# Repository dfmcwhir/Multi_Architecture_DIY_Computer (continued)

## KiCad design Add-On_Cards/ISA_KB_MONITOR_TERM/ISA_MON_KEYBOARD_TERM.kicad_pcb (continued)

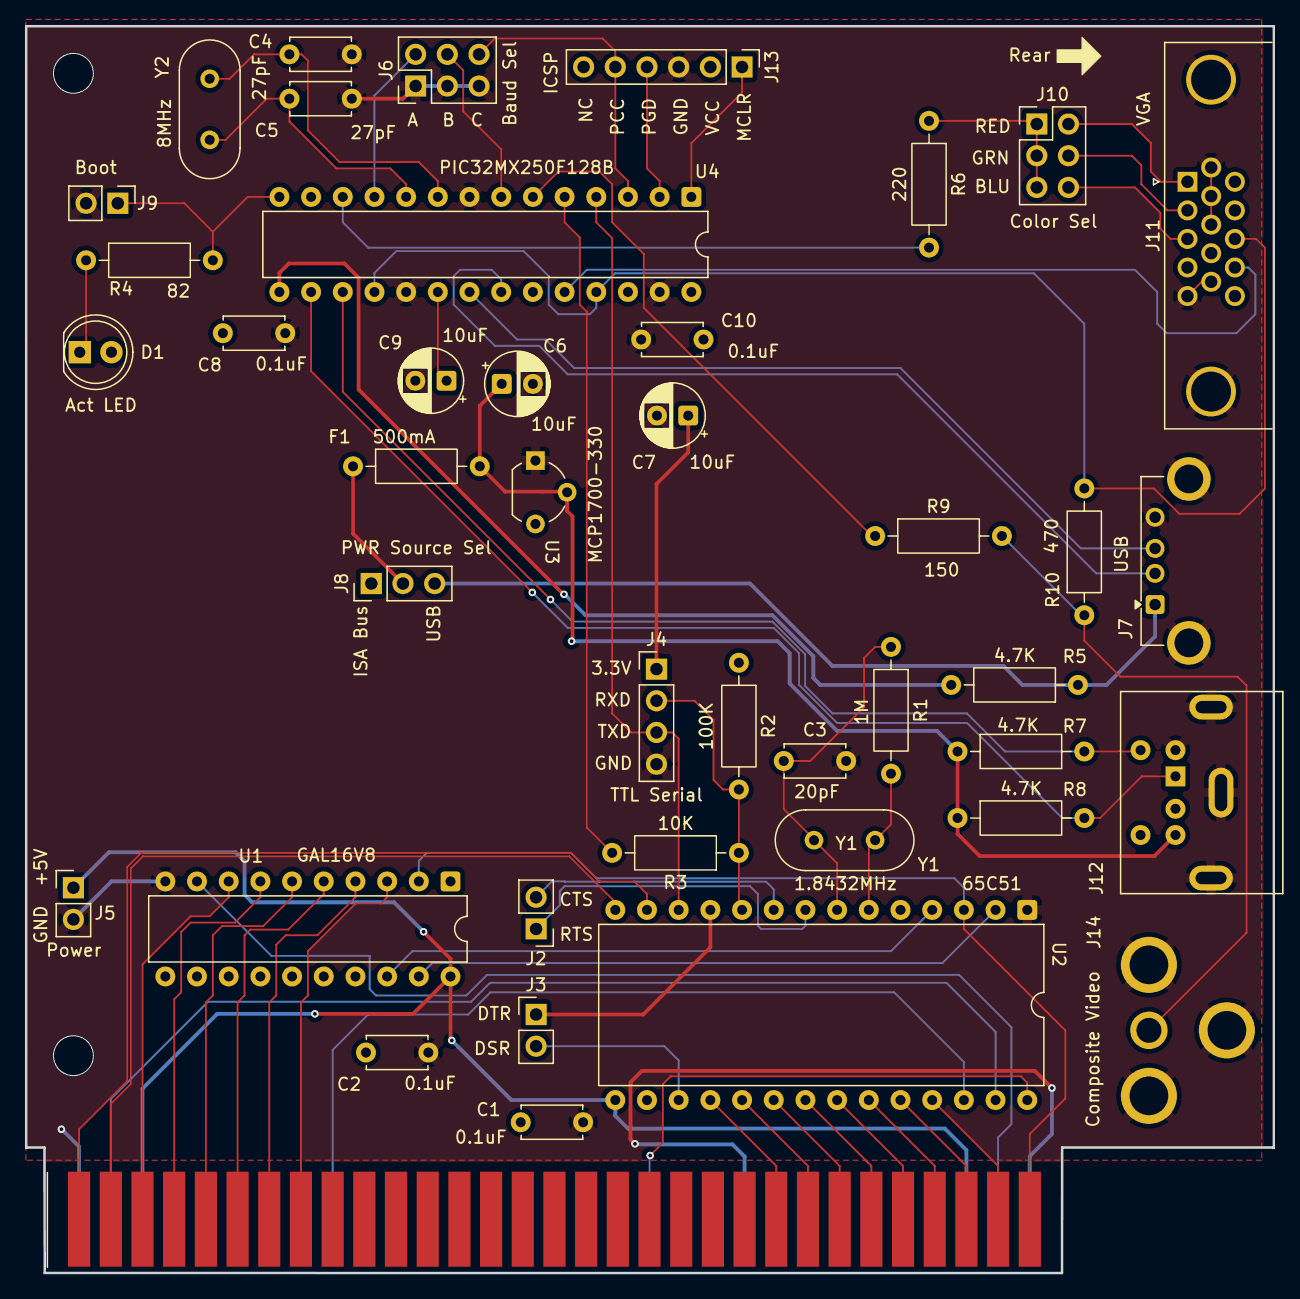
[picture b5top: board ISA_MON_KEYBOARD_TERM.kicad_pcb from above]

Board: 2 copper layers, 100.0 x 99.9 mm, 44 parts (0 on the bottom side), 62 nets.

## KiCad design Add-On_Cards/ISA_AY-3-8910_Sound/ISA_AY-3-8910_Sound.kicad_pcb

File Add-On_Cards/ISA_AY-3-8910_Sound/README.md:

<h2>AY-3-8910 sound card</h2>

<p>This a new card that That is in the process of being tested with the ISA_6502_CPU Rev2 card. For this version of the card the I/O ports A and B were broken out and can be used for general purpose IO. The SPO256 speech chip was added to this version of the board as well.</p>

<h2>Known Bugs</h2>
<p>
  <li>Rev0 of this card ran fine at 2MHz, but to make this card capable of running at higher clock speeds, the PLD introduces a /WAIT signal. For the 6502_CPU_Rev2 card that means the J1 Wait_Sel jumper should be on pins 2-3. However, on the 8085 and Z80 cards that won't work. The current 8085 CPU card doesn't have the /WAIT or /STRETCH signals implemented at all. For the Z80 card both the /WAIT and /STRETCH signals stop the CLK, so the fix is to cut the trace to pin1 of the PLD and attach pin1 of the PLD to the TC (2XOSC) pin on the bus. That modification should also still work when using the 6502_CPU_Rev2 but with JP1 Wait_Sel set to pin 1-2. To make it work with the current 8085 card, it probably requires keeping the CPU speed <3MHz and updating the PLD to not use the /WAIT logic. My current 8085 card uses a 4.9152MHz crystal so the clock is ~2.45MHz, but I haven't tested it with the sound card yet. </li>
<li>Combining the AY3 and SPO256 into a single channel of audio using the mono/stereo jumper doesn't seem to work (I didn't really think it would)</li></p>

<h2>Resources</h2>
<table><thead><tr><th>Address</th><th>Function</th></tr></thead>
<tr><td>7F22</td><td>AY3 Command Register</td></tr>
<tr><td>7F23</td><td>AY3 Data Register</td></tr>
<tr><td>7F26</td><td>SPO256 command/status register</td></tr>
</table>

<p>The SPO256 can use IRQ7 but installing a jumper, but it isn't clear if that will be necessary or desirable.</p>

<h2>Testing Status:</h2>
<li>Basic operation has been tested with the ISA_6502_CPU Rev2 card</li>
<li>AY-3-8910 Port A and B IO hasn't been tested</li>
<li>Amplified output hasn't been tested yet, only the line out</li>
<li>SPO256 speech is pretty quite through the line out, not sure if that is to be expected or if it can be fixed</li>

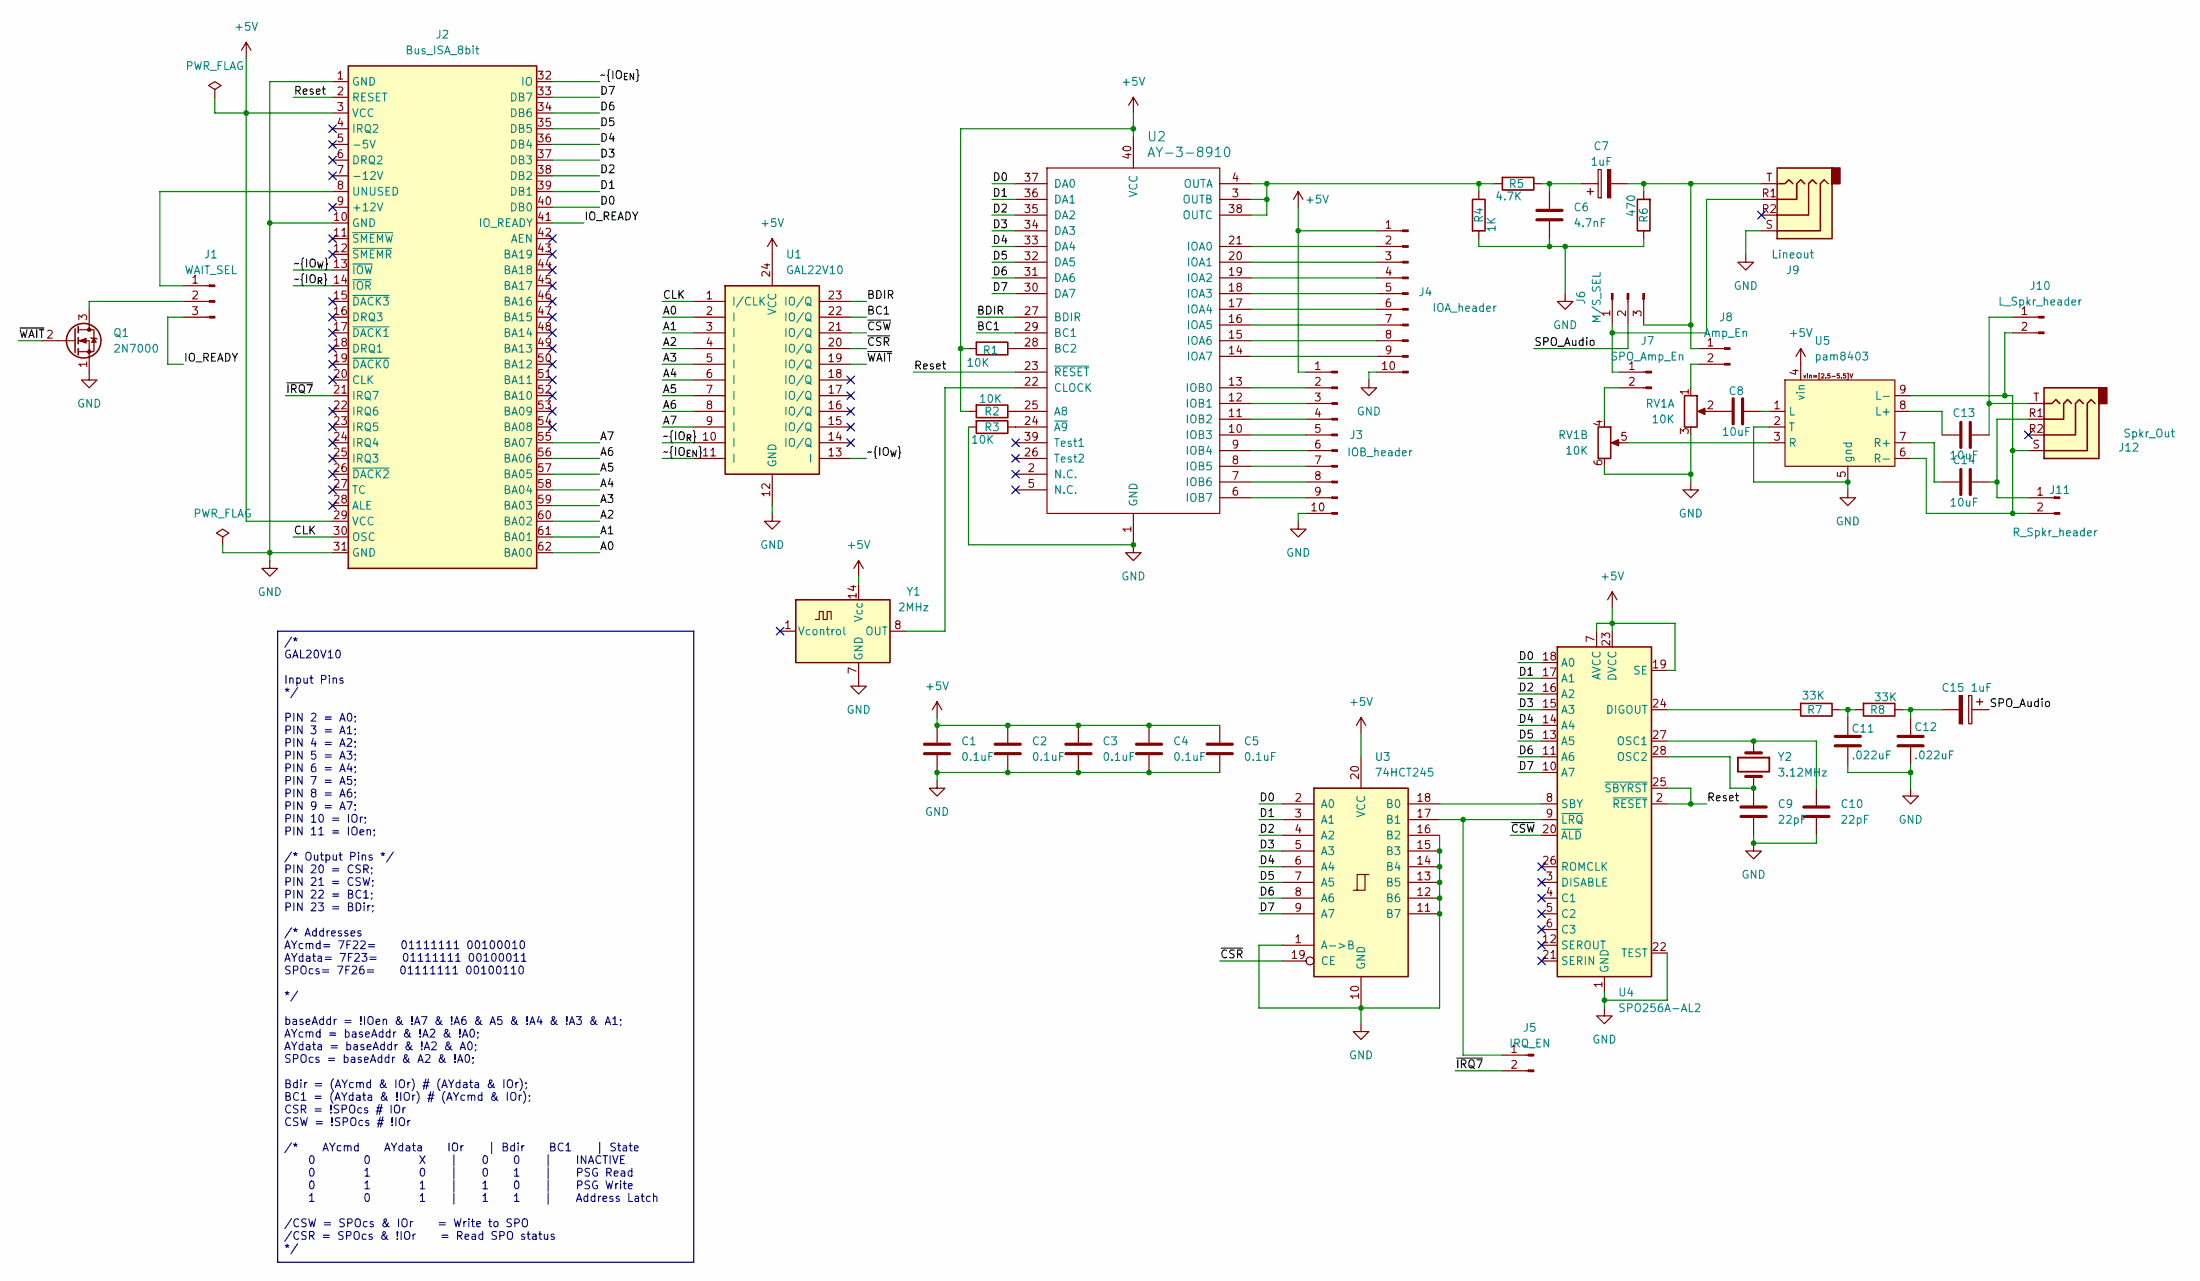
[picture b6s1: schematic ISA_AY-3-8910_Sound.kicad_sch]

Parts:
C1, C2, C3, C4, C5: 0.1uF; C_Disc_D4.7mm_W2.5mm_P5.00mm
C6: 4.7nF; C_Disc_D4.7mm_W2.5mm_P5.00mm
C7, C15: 1uF; CP_Radial_D6.3mm_P2.50mm
C8, C13, C14: 10uF; C_Disc_D4.7mm_W2.5mm_P5.00mm
C9, C10: 22pF; C_Disc_D4.7mm_W2.5mm_P5.00mm
C11, C12: .022uF; C_Disc_D4.7mm_W2.5mm_P5.00mm
J1: WAIT_SEL; PinHeader_1x03_P2.54mm_Vertical
J2: Bus_ISA_8bit; BUS_8-bit_ISA_CARD
J3: IOB_header; PinHeader_1x10_P2.54mm_Vertical
J4: IOA_header; PinHeader_1x10_P2.54mm_Vertical
J5: IRQ_EN; PinHeader_1x02_P2.54mm_Vertical
J6: M/S_SEL; PinHeader_1x03_P2.54mm_Vertical
J7: SPO_Amp_En; PinHeader_1x02_P2.54mm_Vertical
J8: Amp_En; PinHeader_1x02_P2.54mm_Vertical
J9: Lineout; Jack_3.5mm_PJ320E_Horizontal
J10: L_Spkr_header; PinHeader_1x02_P2.54mm_Vertical
J11: Spkr_Out; Jack_3.5mm_PJ320E_Horizontal
J12: R_Spkr_header; PinHeader_1x02_P2.54mm_Vertical
Q1: 2N7000; TO-92_Inline_Wide
R1, R2, R3: 10K; R_Axial_DIN0207_L6.3mm_D2.5mm_P10.16mm_Horizontal
R4: 1K; R_Axial_DIN0207_L6.3mm_D2.5mm_P10.16mm_Horizontal
R5: 4.7K; R_Axial_DIN0207_L6.3mm_D2.5mm_P10.16mm_Horizontal
R6: 470; R_Axial_DIN0207_L6.3mm_D2.5mm_P10.16mm_Horizontal
R7, R8: 33K; R_Axial_DIN0207_L6.3mm_D2.5mm_P10.16mm_Horizontal
RV1: 10K; Potentiometer_Alps_RK097_Dual_Horizontal
U1: GAL22V10; DIP-24_W7.62mm
U2: AY-3-8910; DIP-40_W15.24mm
U3: 74HCT245; DIP-20_W7.62mm
U4: SPO256A-AL2; DIP-28_W15.24mm
U5: pam8403
Y1: 2MHz; Oscillator_DIP-14
Y2: 3.12MHz; Crystal_HC18-U_Vertical

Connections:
+5V: C1.1, C2.1, C3.1, C4.1, C5.1, J2.3 (VCC), J2.29 (VCC), J3.1, J4.1, R1.2, R2.2, U1.24 (VCC), U2.40 (VCC), U3.20 (VCC), U4.7 (AVCC), U4.19 (SE), U4.23 (DVCC), U5.4 (vin), Y1.14 (Vcc)
/A0: J2.62 (BA00), U1.2 (I)
/A1: J2.61 (BA01), U1.3 (I)
/A2: J2.60 (BA02), U1.4 (I)
/A3: J2.59 (BA03), U1.5 (I)
/A4: J2.58 (BA04), U1.6 (I)
/A5: J2.57 (BA05), U1.7 (I)
/A6: J2.56 (BA06), U1.8 (I)
/A7: J2.55 (BA07), U1.9 (I)
/BC1: U1.22 (IO/Q), U2.29 (BC1)
/BDIR: U1.23 (IO/Q), U2.27 (BDIR)
/CLK: J2.30 (OSC), U1.1 (I/CLK)
/D0: J2.40 (DB0), U2.37 (DA0), U3.2 (A0), U4.18 (A0)
/D1: J2.39 (DB1), U2.36 (DA1), U3.3 (A1), U4.17 (A1)
/D2: J2.38 (DB2), U2.35 (DA2), U3.4 (A2), U4.16 (A2)
/D3: J2.37 (DB3), U2.34 (DA3), U3.5 (A3), U4.15 (A3)
/D4: J2.36 (DB4), U2.33 (DA4), U3.6 (A4), U4.14 (A4)
/D5: J2.35 (DB5), U2.32 (DA5), U3.7 (A5), U4.13 (A5)
/D6: J2.34 (DB6), U2.31 (DA6), U3.8 (A6), U4.11 (A6)
/D7: J2.33 (DB7), U2.30 (DA7), U3.9 (A7), U4.10 (A7)
/IO_READY: J1.3, J2.41 (IO_READY)
/Reset: J2.2 (RESET), U2.23 (~RESET), U4.2 (~RESET), U4.25 (~SBYRST)
/SPO_Audio: C15.1, J6.2
/~CSR: U1.20 (IO/Q), U3.19 (CE)
/~CSW: U1.21 (IO/Q), U4.20 (~ALD)
/~IO_{EN}: J2.32 (IO), U1.11 (I)
/~IO_{R}: J2.14 (~IOR), U1.10 (I)
/~IO_{W}: J2.13 (~IOW), U1.13 (I)
/~IRQ7: J2.21 (IRQ7), J5.2
/~WAIT: Q1.2 (G), U1.19 (IO/Q)
GND: C1.2, C2.2, C3.2, C4.2, C5.2, C6.2, C9.2, C10.2, C11.2, C12.2, J2.1 (GND), J2.10 (GND), J2.31 (GND), J3.10, J4.10, J9.S, Q1.1 (S), R3.2, R4.2, R6.1, RV1.3, RV1.6, U1.12 (GND), U2.1 (GND), U3.1 (A->B), U3.10 (GND), U3.11 (B7), U3.12 (B6), U3.13 (B5), U3.14 (B4), U3.15 (B3), U3.16 (B2), U4.1 (GND), U4.22 (TEST), U5.2 (T), U5.5 (gnd), Y1.7 (GND)
unnamed: C6.1, C7.1, R5.1
unnamed: C8.2, RV1.2
unnamed: C11.1, R7.1, R8.2
unnamed: C12.1, C15.2, R8.1
unnamed: J1.1, J2.8 (UNUSED)
unnamed: J1.2, Q1.3 (D)
unnamed: J3.2, U2.13 (IOB0)
unnamed: J3.3, U2.12 (IOB1)
unnamed: J3.4, U2.11 (IOB2)
unnamed: J3.5, U2.10 (IOB3)
unnamed: J3.6, U2.9 (IOB4)
unnamed: J3.7, U2.8 (IOB5)
unnamed: J3.8, U2.7 (IOB6)
unnamed: J3.9, U2.6 (IOB7)
unnamed: J4.2, U2.21 (IOA0)
unnamed: J4.3, U2.20 (IOA1)
unnamed: J4.4, U2.19 (IOA2)
unnamed: J4.5, U2.18 (IOA3)
unnamed: J4.6, U2.17 (IOA4)
unnamed: J4.7, U2.16 (IOA5)
unnamed: J4.8, U2.15 (IOA6)
unnamed: J4.9, U2.14 (IOA7)
unnamed: J5.1, U3.17 (B1), U4.9 (~LRQ)
unnamed: J6.1, J7.1, J9.R1
unnamed: C7.2, J6.3, J8.1, J9.T, R6.2
unnamed: J7.2, RV1.4
unnamed: J8.2, RV1.1
unnamed: C13.1, J10.1, J11.T
unnamed: J10.2, J11.S, J12.2, U5.6 (R-), U5.9 (L-)
unnamed: C14.1, J11.R1, J12.1
unnamed: R2.1, U2.25 (A8)
unnamed: R1.1, U2.28 (BC2)
unnamed: U2.22 (CLOCK), Y1.8 (OUT)
unnamed: R4.1, R5.2, U2.3 (OUTB), U2.4 (OUTA), U2.38 (OUTC)
unnamed: R3.1, U2.24 (~A9)
unnamed: U3.18 (B0), U4.8 (SBY)
unnamed: R7.2, U4.24 (DIGOUT)
unnamed: C10.1, U4.27 (OSC1), Y2.1
unnamed: C9.1, U4.28 (OSC2), Y2.2
unnamed: C8.1, U5.1 (L)
unnamed: C13.2, U5.8 (L+)
unnamed: RV1.5, U5.3 (R)
unnamed: C14.2, U5.7 (R+)

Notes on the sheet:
/* GAL20V10 Input Pins */ PIN 2 = A0; PIN 3 = A1; PIN 4 = A2; PIN 5 = A3; PIN 6 = A4; PIN 7 = A5; PIN 8 = A6; PIN 9 = A7; PIN 10 = IOr; PIN 11 = IOen; /* Output Pins */ PIN 20 = CSR; PIN 21 = CSW; PIN 22 = BC1; PIN 23 = BDir; /* Addresses AYcmd= 7F22= 01111111 00100010 AYdata= 7F23= 01111111 001000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

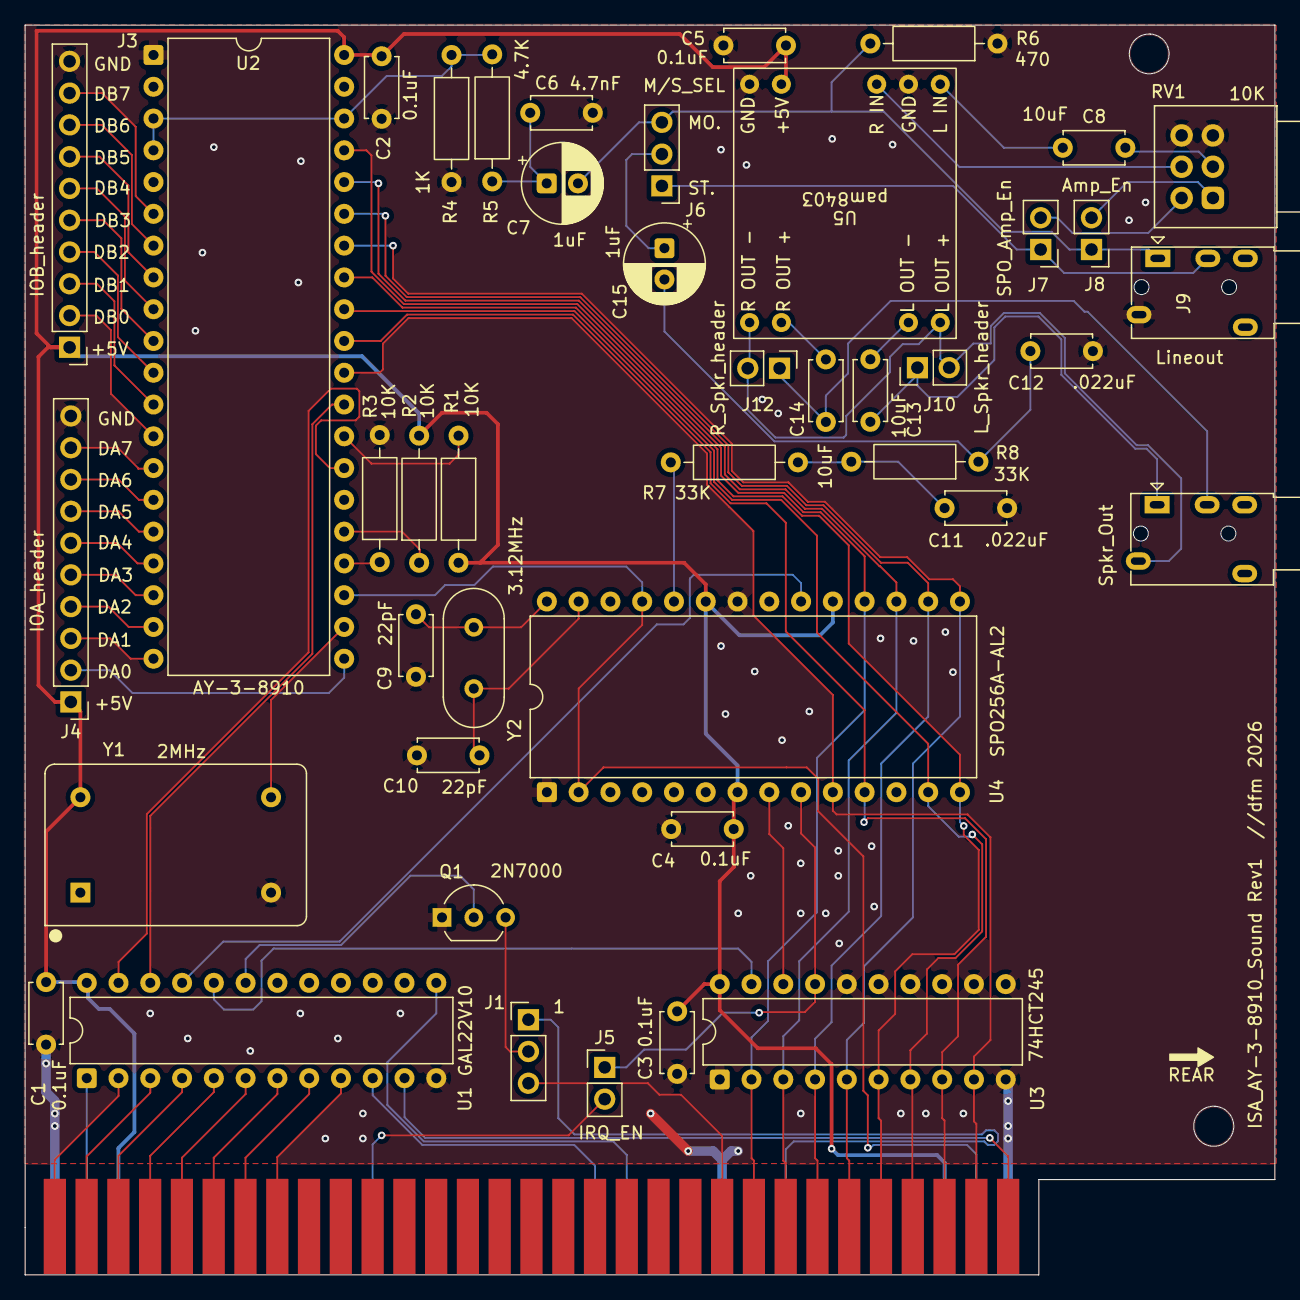
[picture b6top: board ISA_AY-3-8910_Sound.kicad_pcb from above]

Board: 2 copper layers, 99.9 x 99.9 mm, 44 parts (0 on the bottom side), 74 nets.

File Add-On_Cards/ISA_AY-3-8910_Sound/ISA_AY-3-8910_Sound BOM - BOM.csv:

Ref,Qty,Description,Manufacturer,Part number,Digi-Key,Mouser,Footprint (KiCad),Notes,Unit price,Line total,,Total
C1–C5,5,"Capacitor, 0.1 µF ±10%, 50 V, X7R ceramic, radial, 5.08 mm leads",Vishay,K104K15X7RF5TL2,Digi-Key,Mouser,C_Disc_D4.7mm_W2.5mm_P5.00mm,Decoupling. Alt: TDK FG28X7R1E104KRT06 (25 V).,,,,$0.00
C6,1,"Capacitor, 4.7 nF ±10%, 50 V, X7R ceramic, radial, 5.08 mm leads",Vishay,K472K15X7RF5TL2,Digi-Key,Mouser,C_Disc_D4.7mm_W2.5mm_P5.00mm,,,,,
"C7, C15",2,"Capacitor, 1 µF, 50 V, aluminium electrolytic, radial 5 × 11 mm",Panasonic,ECA-1HM010,Digi-Key,Mouser,CP_Radial_D6.3mm_P2.50mm,"Polarized. 1 µF caps are 5 mm across with 2.0 mm leads, which spread easily to the footprint's 2.5 mm. Alt: Nichicon UVR1H010MDD.",,,,
"C8, C13, C14",3,"Capacitor, 10 µF ±20%, 25 V, X5R ceramic, radial, 5.08 mm leads",TDK,FG28X5R1E106MRT06,Digi-Key,Mouser,C_Disc_D4.7mm_W2.5mm_P5.00mm,"The footprint is a non-polarized disc, so a ceramic fits it as drawn. If you use small electrolytics instead, the footprint has no + mark: check the polarity against the schematic.",,,,
"C9, C10",2,"Capacitor, 22 pF ±5%, 50 V, C0G (NP0) ceramic, radial, 5.08 mm leads",Vishay,K220J15C0GF5TL2,Digi-Key,Mouser,C_Disc_D4.7mm_W2.5mm_P5.00mm,Load caps for Y2 (the SPO256's crystal). Alt: TDK FG28C0G1H220JNT06.,,,,
"C11, C12",2,"Capacitor, 22 nF (0.022 µF) ±10%, 50 V, X7R ceramic, radial, 5.08 mm leads",Vishay,K223K15X7RF5TL2,Digi-Key,Mouser,C_Disc_D4.7mm_W2.5mm_P5.00mm,"With R7/R8 (33K), the SPO256's output filter. A film or C0G cap (5 mm leads) holds its value better for audio, if you want it.",,,,
"J1, J6",2,"Pin header, 1 × 3, 2.54 mm, male, straight",Sullins,PRPC003SAAN-RC,Digi-Key,Mouser,PinHeader_1x03_P2.54mm_Vertical,"J1 WAIT_SEL, J6 M/S_SEL.",,,,
"J3, J4",2,"Pin header, 1 × 10, 2.54 mm, male, straight",Sullins,PRPC010SAAN-RC,Digi-Key,Mouser,PinHeader_1x10_P2.54mm_Vertical,"J3 AY port B, J4 port A.",,,,
"J5, J7, J8, J10, J12",5,"Pin header, 1 × 2, 2.54 mm, male, straight",Sullins,PRPC002SAAN-RC,Digi-Key,Mouser,PinHeader_1x02_P2.54mm_Vertical,"J5 IRQ_EN, J7 SPO_Amp_En, J8 Amp_En, J10 / J12 left / right speaker. All the small headers can come from one or two 1 × 40 strips (PRPC040SAAN-RC).",,,,
"(J1, J5–J8)",5,"Jumper shunt, 2.54 mm, 2 positions",Sullins,SPC02SYAN,Digi-Key,Mouser,—,One each for the jumper headers (not the speaker headers).,,,,
"J9, J11",2,"Audio jack, 3.5 mm stereo, PJ-320E style",—,PJ-320E,—,—,Jack_3.5mm_PJ320E_Horizontal,"A generic part (LCSC, AliExpress, Amazon), not stocked by Digi-Key or Mouser. J9 line out, J11 speaker out.",,,,
Q1,1,"MOSFET, N-channel, 60 V, 200 mA, 2N7000, TO-92",onsemi,2N7000TA,Digi-Key,Mouser,TO-92_Inline_Wide,"Pulls IOREADY low (wait states). Any 2N7000 will do (Microchip 2N7000-G, Diodes 2N7000).",,,,
R1–R3,3,"Resistor, 10 kΩ, 1/4 W, 5%, carbon film, axial",Stackpole,CF14JT10K0,Digi-Key,Mouser,R_Axial_DIN0207_L6.3mm_D2.5mm_P10.16mm_Horizontal,,,,,
R4,1,"Resistor, 1 kΩ, 1/4 W, 5%, carbon film, axial",Stackpole,CF14JT1K00,Digi-Key,Mouser,R_Axial_DIN0207_L6.3mm_D2.5mm_P10.16mm_Horizontal,,,,,
R5,1,"Resistor, 4.7 kΩ, 1/4 W, 5%, carbon film, axial",Stackpole,CF14JT4K70,Digi-Key,Mouser,R_Axial_DIN0207_L6.3mm_D2.5mm_P10.16mm_Horizontal,,,,,
R6,1,"Resistor, 470 Ω, 1/4 W, 5%, carbon film, axial",Stackpole,CF14JT470R,Digi-Key,Mouser,R_Axial_DIN0207_L6.3mm_D2.5mm_P10.16mm_Horizontal,,,,,
"R7, R8",2,"Resistor, 33 kΩ, 1/4 W, 5%, carbon film, axial",Stackpole,CF14JT33K0,Digi-Key,Mouser,R_Axial_DIN0207_L6.3mm_D2.5mm_P10.16mm_Horizontal,"The SPO256's output filter, with C11/C12.",,,,
RV1,1,"Potentiometer, 10 kΩ, dual gang, audio (log) taper, Alps RK097, PCB pins",Alps Alpine,RK09712200HA,Digi-Key,Mouser,My_Parts:Potentiometer_Alps_RK097_Dual_Horizontal,Stereo volume. RK097 versions differ in shaft length and style and in bushing: pick the one that suits your knob and panel. Audio taper suits a volume control.,,,,
U1,1,"PLD, 22V10, 7.5 ns, DIP-24 0.3"" (GAL22V10 equivalent)",Microchip,ATF22V10C-7PX,Digi-Key,Mouser,DIP-24_W7.62mm,Replaces the GAL22V10.,,,,
U2,1,"Programmable sound generator, AY-3-8910, DIP-40",General Instrument (obsolete),AY-3-8910,—,—,DIP-40_W15.24mm,"Long out of production: eBay or AliExpress, where many are relabelled or fake; buy from a seller who tests them. A Yamaha YM2149F works in its place.",,,,
U3,1,"Octal bus transceiver, 74HCT245, DIP-20",Texas Instruments,SN74HCT245N,Digi-Key,Mouser,DIP-20_W7.62mm,"Reads the SPO256's status (STBY, /LRQ).",,,,
U4,1,"Speech processor, SPO256A-AL2, DIP-28 0.6""",General Instrument (obsolete),SPO256A-AL2,—,—,DIP-28_W15.24mm,"Long out of production: eBay, or Speechchips.com, which sells tested ones.",,,,
U5,1,"Class D stereo amplifier module, PAM8403, 2 × 3 W",—,PAM8403 module,—,—,pam8403:pam8403,"A generic module (Amazon, AliExpress). Check that its pin order matches your footprint; layouts vary between sellers.",,,,
Y1,1,"Oscillator, 2 MHz, 5 V, full-size DIP-14 metal can",ECS,ECS-100AX-020,Digi-Key,Mouser,Oscillator_DIP-14,The AY's clock.,,,,
Y2,1,"Crystal, 3.072 MHz, HC-49/US, 18 pF (in place of 3.12 MHz)",Abracon,ABLS-LR-3.072MHZ-T,Digi-Key,Mouser,Crystal_HC18-U_Vertical,"3.12 MHz crystals aren't stocked. 3.072 MHz is 1.5% low, which you won't hear. The short HC-49/US has the same lead spacing as the footprint. 3.579545 MHz (common) also works, but the voice comes out about 15% higher and faster.",,,,
(U1),1,"IC socket, DIP-24, 0.3"", machined pin",Mill-Max,110-43-324-41-001000,Digi-Key,Mouser,—,"Optional; the PLD comes out for reprogramming.",,,,
(U2),1,"IC socket, DIP-40, 0.6"", machined pin",Mill-Max,110-43-640-41-001000,Digi-Key,Mouser,—,Worth having: the AY is hard to replace.,,,,
(U3),1,"IC socket, DIP-20, 0.3"", machined pin",Mill-Max,110-43-320-41-001000,Digi-Key,Mouser,—,Optional.,,,,
(U4),1,"IC socket, DIP-28, 0.6"", machined pin",Mill-Max,110-43-628-41-001000,Digi-Key,Mouser,—,Worth having: the SPO256 is hard to replace.,,,,
(Y1),1,"IC socket, DIP-14, 0.3"", machined pin",Mill-Max,110-43-314-41-001000,Digi-Key,Mouser,—,Optional. Takes the full-size oscillator's 4 pins.,,,,

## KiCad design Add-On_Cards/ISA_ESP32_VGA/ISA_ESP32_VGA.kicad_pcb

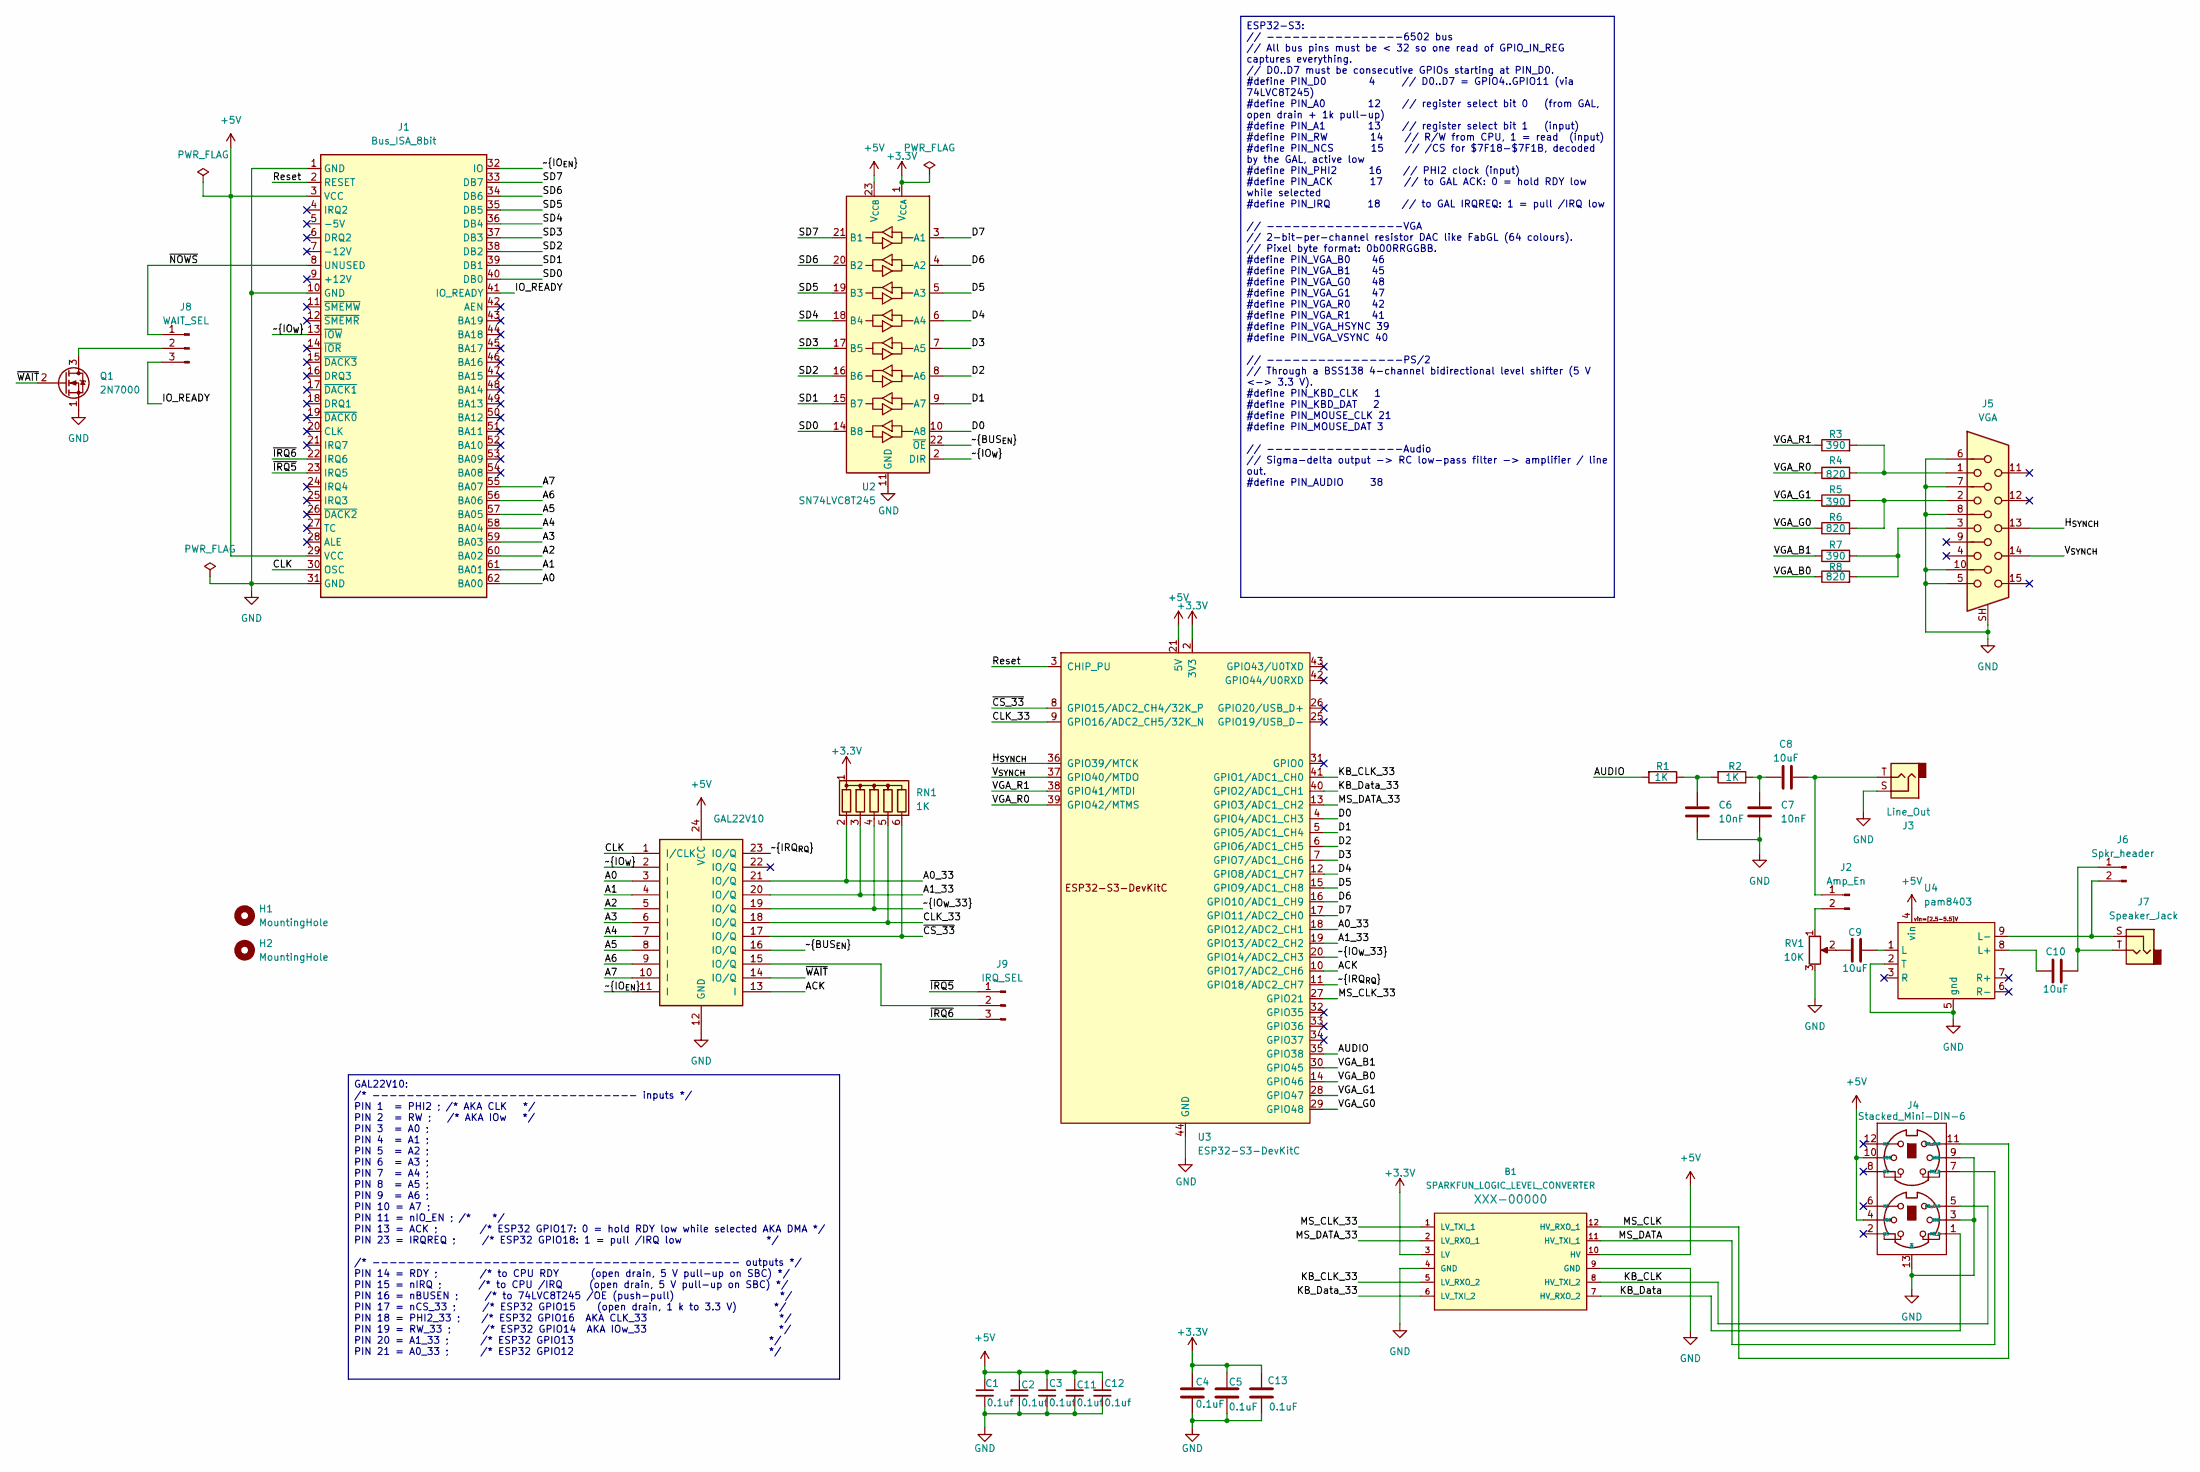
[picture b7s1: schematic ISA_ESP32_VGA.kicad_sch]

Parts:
B1: SPARKFUN_LOGIC_LEVEL_CONVERTER; 4_Chan_Logic_level_shifter_module
C1, C2, C3, C11, C12: 0.1uf; C_Disc_D4.7mm_W2.5mm_P5.00mm; Voltage 50V; Tolerance 5%
C4, C5, C13: 0.1uF; C_Disc_D4.7mm_W2.5mm_P5.00mm
C6, C7: 10nF; C_Disc_D4.7mm_W2.5mm_P5.00mm
C8, C9, C10: 10uF; C_Disc_D4.7mm_W2.5mm_P5.00mm
H1, H2: MountingHole; MountingHole_3.2mm_M3
J1: Bus_ISA_8bit; BUS_8-bit_ISA
J2: Amp_En; PinHeader_1x02_P2.54mm_Vertical
J3: Line_Out; Jack_3.5mm_PJ320E_Horizontal
J4: Stacked_Mini-DIN-6; Stacked_Mini-DIN_Female_6Pin_2rows
J5: VGA; DSUB-15-HD_Socket_Horizontal_P2.29x1.90mm_EdgePinOffset3.03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
J6: Spkr_header; PinHeader_1x02_P2.54mm_Vertical
J7: Speaker_Jack; Jack_3.5mm_PJ320E_Horizontal
J8: WAIT_SEL; PinHeader_1x03_P2.54mm_Vertical
J9: IRQ_SEL; PinHeader_1x03_P2.54mm_Vertical
Q1: 2N7000; TO-92_Inline_Wide
R1, R2: 1K; R_Axial_DIN0204_L3.6mm_D1.6mm_P5.08mm_Horizontal
R3, R5, R7: 390; R_Axial_DIN0204_L3.6mm_D1.6mm_P5.08mm_Horizontal
R4, R6, R8: 820; R_Axial_DIN0204_L3.6mm_D1.6mm_P5.08mm_Horizontal
RN1: 1K; R_Array_SIP6
RV1: 10K; Potentiometer_Alps_RK097_Dual_Horizontal
U1: GAL22V10; DIP-24_W7.62mm
U2: SN74LVC8T245; SOP-24_7.5x15.4mm_P1.27mm
U3: ESP32-S3-DevKitC; ESP32-S2-DevKitC-1
U4: pam8403

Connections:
+3.3V: B1.3 (LV), C4.1, C5.1, C13.1, RN1.1 (common), U2.1 (V_{CCA}), U3.1 (3V3), U3.2 (3V3)
+5V: B1.10 (HV), C1.1, C2.1, C3.1, C11.1, C12.1, J1.3 (VCC), J1.29 (VCC), J4.4 (VCC), J4.10 (VCC), U1.24 (VCC), U2.23 (V_{CCB}), U2.24 (V_{CCB}), U3.21 (5V), U4.4 (vin)
/A0: J1.62 (BA00), U1.3 (I)
/A0_33: RN1.2 (R1), U1.21 (IO/Q), U3.18 (GPIO12/ADC2_CH1)
/A1: J1.61 (BA01), U1.4 (I)
/A1_33: RN1.3 (R2), U1.20 (IO/Q), U3.19 (GPIO13/ADC2_CH2)
/A2: J1.60 (BA02), U1.5 (I)
/A3: J1.59 (BA03), U1.6 (I)
/A4: J1.58 (BA04), U1.7 (I)
/A5: J1.57 (BA05), U1.8 (I)
/A6: J1.56 (BA06), U1.9 (I)
/A7: J1.55 (BA07), U1.10 (I)
/ACK: U1.13 (I), U3.10 (GPIO17/ADC2_CH6)
/AUDIO: R1.2, U3.35 (GPIO38)
/CLK: J1.30 (OSC), U1.1 (I/CLK)
/CLK_33: RN1.5 (R4), U1.18 (IO/Q), U3.9 (GPIO16/ADC2_CH5/32K_N)
/D0: U2.10 (A8), U3.4 (GPIO4/ADC1_CH3)
/D1: U2.9 (A7), U3.5 (GPIO5/ADC1_CH4)
/D2: U2.8 (A6), U3.6 (GPIO6/ADC1_CH5)
/D3: U2.7 (A5), U3.7 (GPIO7/ADC1_CH6)
/D4: U2.6 (A4), U3.12 (GPIO8/ADC1_CH7)
/D5: U2.5 (A3), U3.15 (GPIO9/ADC1_CH8)
/D6: U2.4 (A2), U3.16 (GPIO10/ADC1_CH9)
/D7: U2.3 (A1), U3.17 (GPIO11/ADC2_CH0)
/H_{SYNCH}: J5.13, U3.36 (GPIO39/MTCK)
/IO_READY: J1.41 (IO_READY), J8.3
/KB_CLK: B1.8 (HV_TXI_2), J4.5 (KB_CLK)
/KB_CLK_33: B1.5 (LV_RXO_2), U3.41 (GPIO1/ADC1_CH0)
/KB_Data: B1.7 (HV_RXO_2), J4.1 (KB_D)
/KB_Data_33: B1.6 (LV_TXI_2), U3.40 (GPIO2/ADC1_CH1)
/MS_CLK: B1.12 (HV_RXO_1), J4.11 (MS_CLK)
/MS_CLK_33: B1.1 (LV_TXI_1), U3.27 (GPIO21)
/MS_DATA: B1.11 (HV_TXI_1), J4.7 (MS_D)
/MS_DATA_33: B1.2 (LV_RXO_1), U3.13 (GPIO3/ADC1_CH2)
/Reset: J1.2 (RESET), U3.3 (CHIP_PU)
/SD0: J1.40 (DB0), U2.14 (B8)
/SD1: J1.39 (DB1), U2.15 (B7)
/SD2: J1.38 (DB2), U2.16 (B6)
/SD3: J1.37 (DB3), U2.17 (B5)
/SD4: J1.36 (DB4), U2.18 (B4)
/SD5: J1.35 (DB5), U2.19 (B3)
/SD6: J1.34 (DB6), U2.20 (B2)
/SD7: J1.33 (DB7), U2.21 (B1)
/VGA_B0: R8.1, U3.14 (GPIO46)
/VGA_B1: R7.1, U3.30 (GPIO45)
/VGA_G0: R6.1, U3.29 (GPIO48)
/VGA_G1: R5.1, U3.28 (GPIO47)
/VGA_R0: R4.1, U3.39 (GPIO42/MTMS)
/VGA_R1: R3.1, U3.38 (GPIO41/MTDI)
/V_{SYNCH}: J5.14, U3.37 (GPIO40/MTDO)
/~BUS_{EN}: U1.16 (IO/Q), U2.22 (~OE)
/~CS_33: RN1.6 (R5), U1.17 (IO/Q), U3.8 (GPIO15/ADC2_CH4/32K_P)
/~IO_{EN}: J1.32 (IO), U1.11 (I)
/~IO_{W_33}: RN1.4 (R3), U1.19 (IO/Q), U3.20 (GPIO14/ADC2_CH3)
/~IO_{W}: J1.13 (~IOW), U1.2 (I), U2.2 (DIR)
/~IRQ5: J1.23 (IRQ5), J9.1
/~IRQ6: J1.22 (IRQ6), J9.3
/~IRQ_{RQ}: U1.23 (IO/Q), U3.11 (GPIO18/ADC2_CH7)
/~NOWS: J1.8 (UNUSED), J8.1
/~WAIT: Q1.2 (G), U1.14 (IO/Q)
GND: B1.4 (GND), B1.9 (GND), C1.2, C2.2, C3.2, C4.2, C5.2, C6.2, C7.2, C11.2, C12.2, C13.2, J1.1 (GND), J1.10 (GND), J1.31 (GND), J3.S, J4.3 (GND), J4.9 (GND), J4.13 (SH), J5.5, J5.6, J5.7, J5.8, J5.10, J5.SH, Q1.1 (S), RV1.3, U1.12 (GND), U2.11 (GND), U2.12 (GND), U2.13 (GND), U3.22 (GND), U3.23 (GND), U3.24 (GND), U3.44 (GND), U4.2 (T), U4.5 (gnd)
unnamed: C6.1, R1.1, R2.2
unnamed: C7.1, C8.1, R2.1
unnamed: C9.2, RV1.2
unnamed: C8.2, J2.1, J3.T
unnamed: J2.2, RV1.1
unnamed: J5.1, R3.2, R4.2
unnamed: J5.2, R5.2, R6.2
unnamed: J5.3, R7.2, R8.2
unnamed: C10.1, J6.1, J7.T
unnamed: J6.2, J7.S, U4.9 (L-)
unnamed: J8.2, Q1.3 (D)
unnamed: J9.2, U1.15 (IO/Q)
unnamed: C9.1, U4.1 (L)
unnamed: C10.2, U4.8 (L+)

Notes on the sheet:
ESP32-S3: // ----------------6502 bus // All bus pins must be < 32 so one read of GPIO_IN_REG captures everything. // D0..D7 must be consecutive GPIOs starting at PIN_D0. #define PIN_D0 4 // D0..D7 = GPIO4..GPIO11 (via 74LVC8T245) #define PIN_A0 12 // register select bit 0 (from GAL, open drain + 1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
GAL22V10: /* ------------------------------- inputs */ PIN 1 = PHI2 ; /* AKA CLK */ PIN 2 = RW ; /* AKA IOw */ PIN 3 = A0 ; PIN 4 = A1 ; PIN 5 = A2 ; PIN 6 = A3 ; PIN 7 = A4 ; PIN 8 = A5 ; PIN 9 = A6 ; PIN 10 = A7 ; PIN 11 = nIO_EN ; /* */ PIN 13 = ACK ; /* ESP32 GPIO17: 0 = hold RDY low while sele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

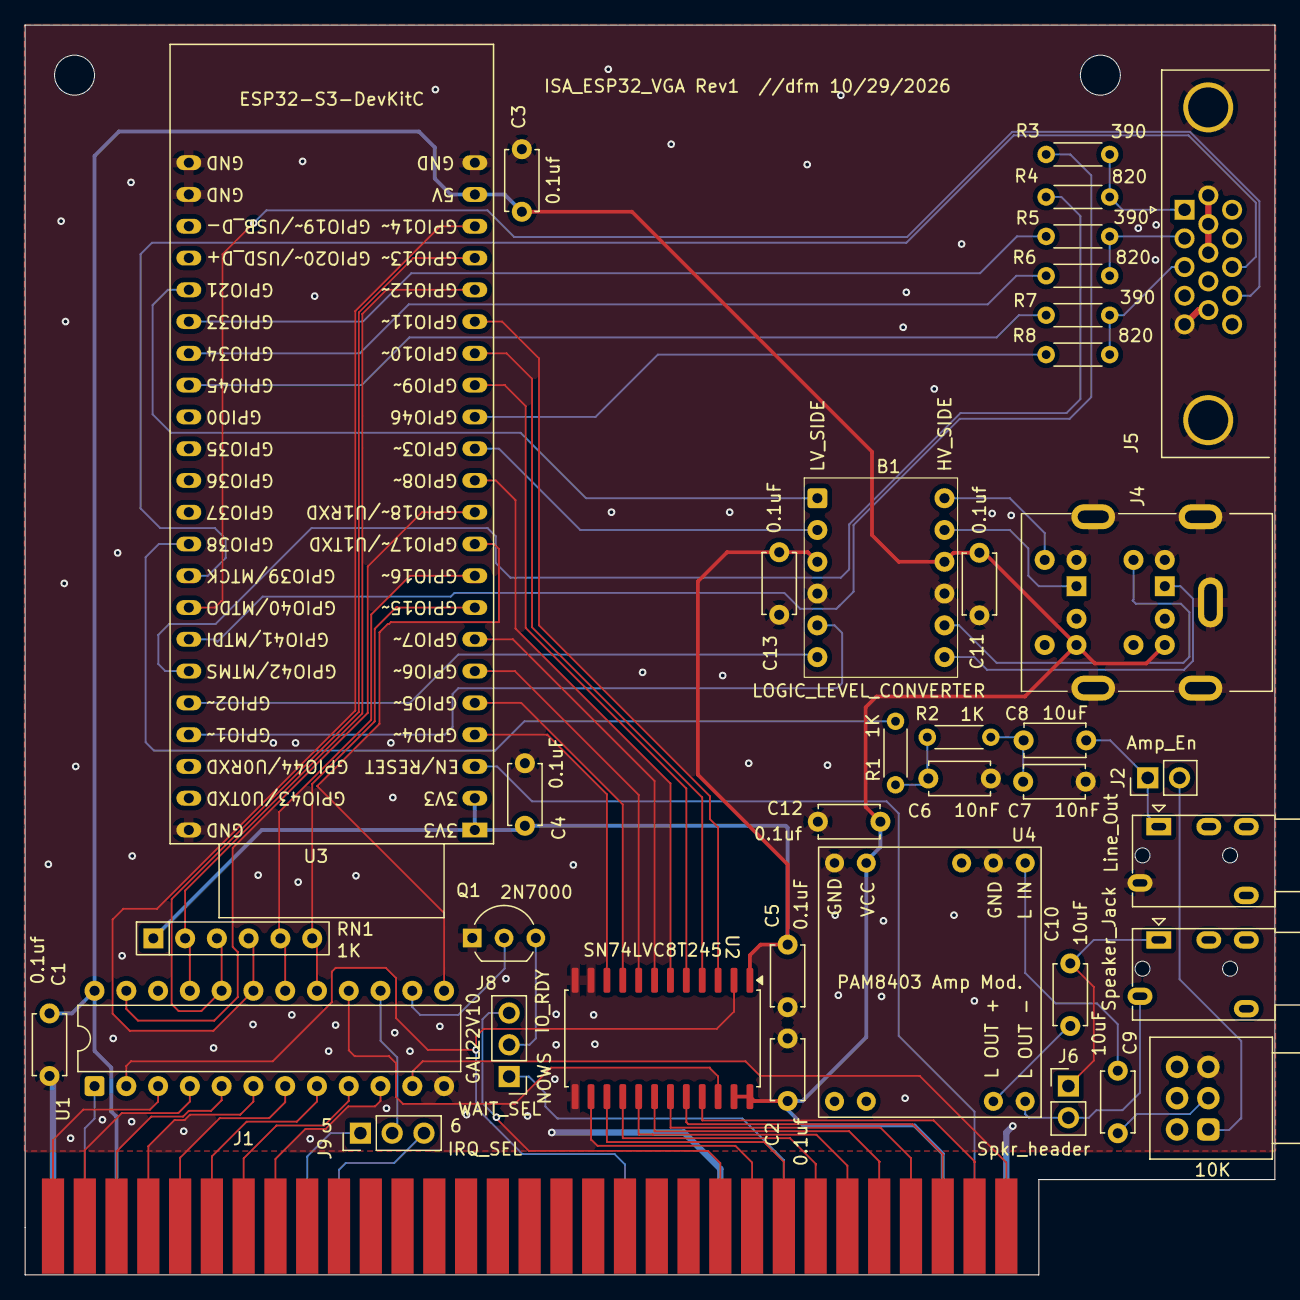
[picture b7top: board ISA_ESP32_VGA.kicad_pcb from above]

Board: 2 copper layers, 99.9 x 99.9 mm, 40 parts (0 on the bottom side), 75 nets.
